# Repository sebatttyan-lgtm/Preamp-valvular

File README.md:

# Preamplificador valvular

amplificador valvular estéreo con 2 válvulas de vacío y control de volumen por medio de 2 potenciómetros instalados en la placa, junto a borneras de alimentación de válvulas y filamento, entrada y salida. El circuito está basado en el kit de Lothye [modulo preamplificador](https://tienda.starware.com.ar/producto/modulo-preamplificador-valvular-lothye-6j1-12v-ac-diy-para-armar-kit-partes/) , pero separando la fuente de alimentación de el preamplificador y el preamplificador en sí mismo.

## Integrantes

**Perez Sebastian Alessandro.**

## Materiales (placa de preamplificador)

### resistencias

| valor | cantidad | potencia | tipo 
| :------------: | :------------: | :---------: | :---------- |
| 4k7Ω | 4 | 1/2W | fija |
| 470kΩ | 2 | 1/2W | fija |
| 200Ω | 2 | 1/2W | fija |
| 100kΩ | 2 | 1/2W | fija |
| 100kΩ | 2 | - | potenciómetro (logarítmico) |

### Capacitores

- **4 capacitores de 1μF**

### Conectores

- **3 bornera de 2 entradas.** 
- **1 borneras de 3 entradas.**
  
### Extras

- **2 valvulas de vacio 6j1 o similares.** 

## PLACA DE CIRCUITO IMPRESO (PCB)

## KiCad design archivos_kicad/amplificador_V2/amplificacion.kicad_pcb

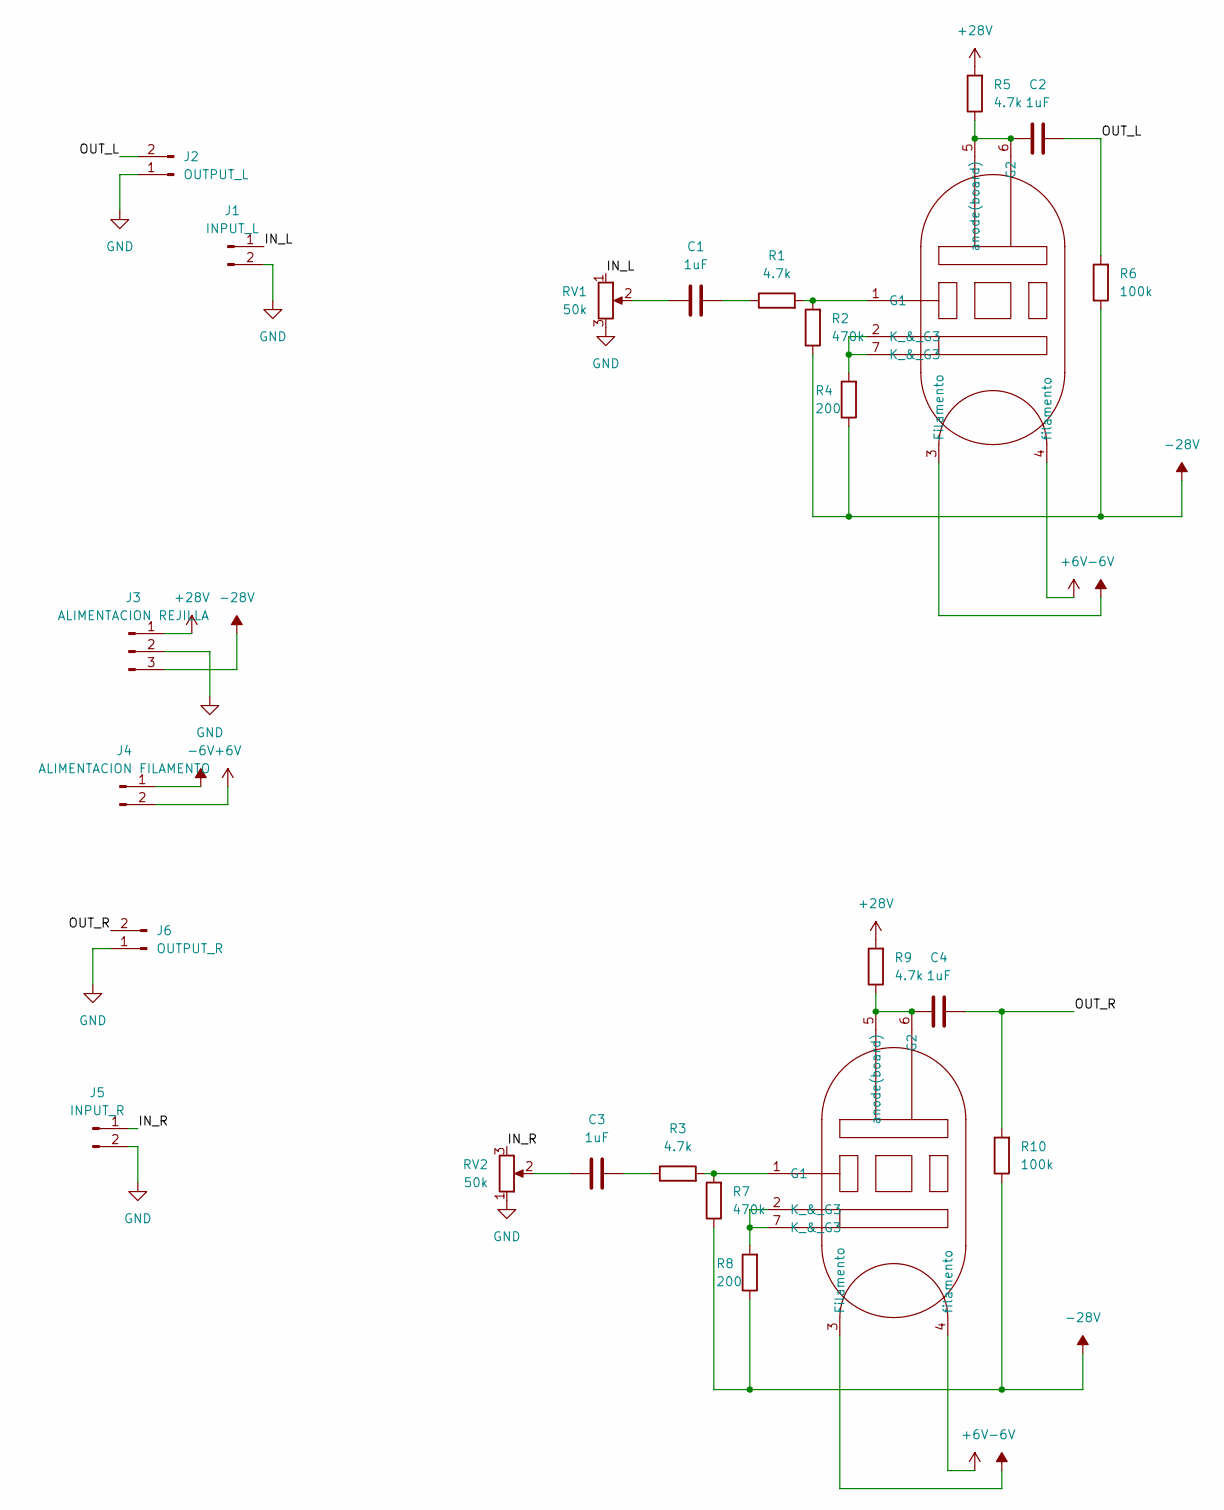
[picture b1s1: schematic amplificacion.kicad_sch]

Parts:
C1, C2, C3, C4: 1uF; C_Disc_D6.0mm_W2.5mm_P5.00mm
J1: INPUT_L; TerminalBlock_Phoenix_MKDS-1,5-2-5.08_1x02_P5.08mm_Horizont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
J2: OUTPUT_L; TerminalBlock_Phoenix_MKDS-1,5-2-5.08_1x02_P5.08mm_Horizont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
J3: ALIMENTACION REJILLA; TerminalBlock_Phoenix_MKDS-1,5-3-5.08_1x03_P5.08mm_Horizont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
J4: ALIMENTACION FILAMENTO; TerminalBlock_Phoenix_MKDS-1,5-2-5.08_1x02_P5.08mm_Horizont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
J5: INPUT_R; TerminalBlock_Phoenix_MKDS-1,5-2-5.08_1x02_P5.08mm_Horizont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
J6: OUTPUT_R; TerminalBlock_Phoenix_MKDS-1,5-2-5.08_1x02_P5.08mm_Horizont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
R1, R3, R5, R9: 4.7k; R_Axial_DIN0207_L6.3mm_D2.5mm_P10.16mm_Horizontal
R2, R7: 470k; R_Axial_DIN0207_L6.3mm_D2.5mm_P10.16mm_Horizontal
R4, R8: 200; R_Axial_DIN0207_L6.3mm_D2.5mm_P10.16mm_Horizontal
R6, R10: 100k; R_Axial_DIN0207_L6.3mm_D2.5mm_P10.16mm_Horizontal
RV1, RV2: 50k; TRIM_WH148-1A-2-18T-L20
U1, U2: Valve_Mini_P

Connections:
+6V: J4.2, U1.4 (filamento), U2.4 (filamento)
+28V: J3.1, R5.2, R9.2
-6V: J4.1, U1.3 (Filamento), U2.3 (Filamento)
-28V: J3.3, R2.1, R4.1, R6.1, R7.1, R8.1, R10.1
/IN_L: J1.1, RV1.1
/IN_R: J5.1, RV2.3
/OUT_L: C2.2, J2.2, R6.2
/OUT_R: C4.2, J6.2, R10.2
GND: J1.2, J2.1, J3.2, J5.2, J6.1, RV1.3, RV2.1
unnamed: C1.1, R1.1
unnamed: C1.2, RV1.2
unnamed: C3.1, R3.1
unnamed: C3.2, RV2.2
unnamed: R4.2, U1.2 (K_&_G3), U1.7 (K_&_G3)
unnamed: R8.2, U2.2 (K_&_G3), U2.7 (K_&_G3)
unnamed: R1.2, R2.2, U1.1 (G1)
unnamed: C2.1, R5.1, U1.5 (anode(board)), U1.6 (G2)
unnamed: R3.2, R7.2, U2.1 (G1)
unnamed: C4.1, R9.1, U2.5 (anode(board)), U2.6 (G2)

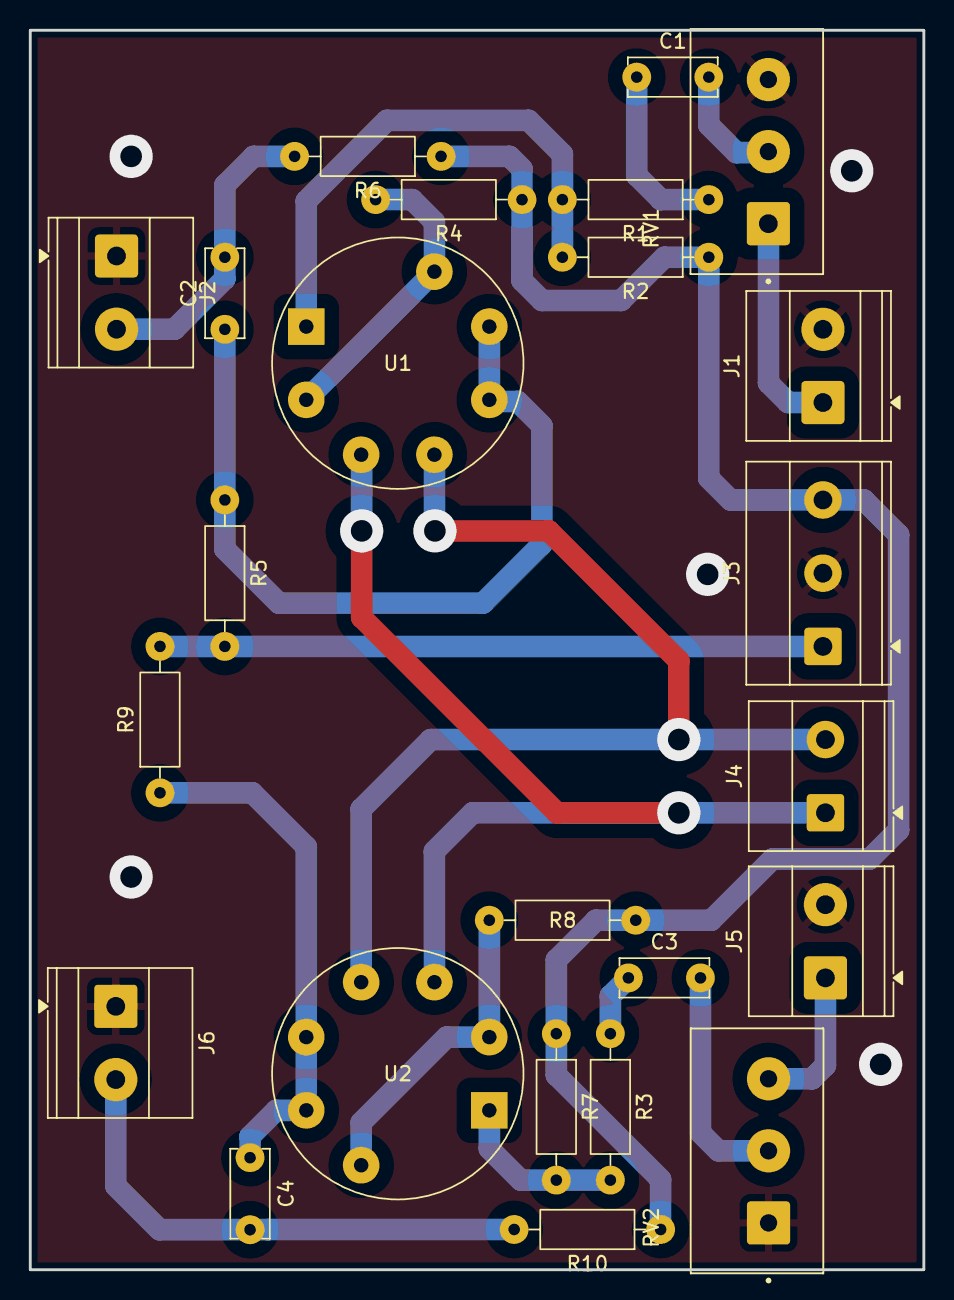
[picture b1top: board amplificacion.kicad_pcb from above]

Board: 2 copper layers, 62.0 x 86.0 mm, 24 parts (0 on the bottom side), 19 nets.
